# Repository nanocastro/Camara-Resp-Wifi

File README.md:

# Cámara de respiración de suelo

Prototipo portátil y de bajo costo para medir el flujo de CO2, la temperatura y la humedad del suelo y estimar su actividad microbiana.  

Este prototipo es parte del trabajo que estamos desarrollando en el [Laboratorio agroecológico abierto](https://regosh.libres.cc/proyectos/lab-agroeco-abierto/) y el nodo [ReGOSH de Mendoza](https://regosh.libres.cc/).

Su desarrollo está basado en el [prototipo abierto de Hackteria](https://www.hackteria.org/wiki/CO2_Soil_Respiration_Chamber).  

El costo de este prototipo es de 2 órdenes de magnitud menor que el de una [cámara comercial](https://gitlab.com/nanocastro/camara-respiracion-suelo/-/blob/master/Presupuestos%20Nro%2012426.PDF).  

## Prototipos
Estos prototipos están aún en fase de desarrollo. Necesitamos testear en campo y mejorar la documentación y el diseño.

### Prototipo actual - Versión Mendoza

Este prototipo utiliza el sensor de CO2 infrarrojo MH-Z19B que se coloca en el interior de una cámara para medir el flujo de CO2 y es controlado por una placa Arduino UNO. Los datos son transmitidos por bluetooth a un script de python que recibe los datos, los grafica en tiempo real y calcula la regresión lineal de un intervalo deseado. El dispositivo mide también la temperatura y la humedad de suelo

> [Aquí la documentación completa](/Version2-Mza) 

### Primer prototipo - Residencia Porto Alegre

[Primer prototipo](/Versión1-%20PA) desarrollado en el marco de la residencia ReGOSH (Porto Alegre) financiadas por CYTED.   
Este dispositivo utiliza un sensor MH-Z16 y una placa Teensy 4.0. Los datos se visualizan en una pantalla OLED

### Cómo funciona y para que sirve una cámara de respiración de suelo?
[Aqui](/Referencias) puedes encontrar algunos documentos que explican el funcionamiento de las cámaras de respiración de suelo y presentan algunos de sus usos

### Licencia 
Este proyecto es de código abierto y se libera bajo [licencia CERN para hardware abierto](https://gitlab.com/nanocastro/camara-respiracion-suelo/-/blob/master/License). 

### Te interesa colaborar?

Si te interesa el proyecto y quisieras colaborar podes escribirnos a 

ferhcastro at gmail.com o pcremades at gmail.com

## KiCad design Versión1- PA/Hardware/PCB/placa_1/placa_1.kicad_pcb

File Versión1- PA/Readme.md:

### Primer prototipo - Residencia Porto Alegre

[Primer prototipo](/Versión1-%20PA) desarrollado en el marco de la residencia ReGOSH (Porto Alegre) financiadas por CYTED.   
Este dispositivo utiliza un sensor MH-Z16 y una placa Teensy 4.0. Los datos se visualizan en una pantalla OLED

# Camara respiración de suelo - Residencia Porto Alegre

### Diseço de placa_ 

Acá se puede ver la placa en pcb de la cámara de respiración, como algunos complementos que fueron creados para el mismo 
https://gitlab.com/nodo-mendoza/camara-respiracion-suelo/tree/master/hardware/electronics
También pueden ver algunos inconvenientes que se nos presentaron aquí https://gitlab.com/nodo-mendoza/camara-respiracion-suelo/issues/3

### Fresadora_

Los archivos digitales para la fresadora se hicieron tomando como guía el siguiente trabajo
http://cta.if.ufrgs.br/projects/estacao-meteorologica-modular/wiki/Placa_de_Controle,
donde se modificaron parámetros de acuerdo a las características específicas del proyecto como del tipo de fresadora utilizada.
Lo anterior descripto se puede observar aqui https://gitlab.com/nodo-mendoza/camara-respiracion-suelo/tree/master/hardware/electronics/placa_1/gCode/ngc
imágenes dd157eda80d9fbdee688e2e542551893808dbe02

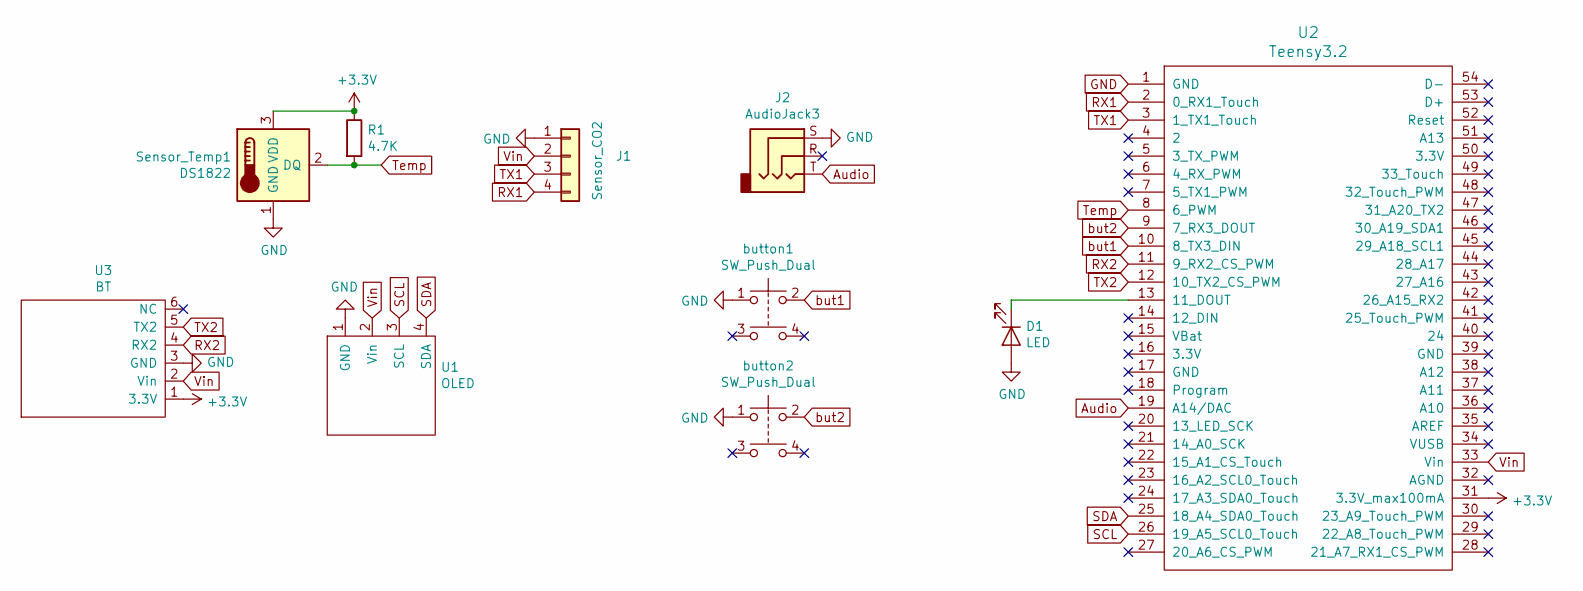
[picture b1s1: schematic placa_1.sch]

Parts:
D1: LED; LED_D3.0mm_IRBlack
J1: Sensor_CO2; PinHeader_1x04_P2.54mm_Vertical
J2: AudioJack3; AudioJack
R1: 4.7K; R_Axial_DIN0207_L6.3mm_D2.5mm_P7.62mm_Horizontal
Sensor_Temp1: DS1822; PinHeader_1x03_P2.54mm_Vertical
U1: OLED; PinHeader_1x04_P2.54mm_Vertical
U2: Teensy3.2; Teensy30_31_32_LC
U3: BT; PinHeader_1x06_P2.54mm_Vertical
button1, button2: SW_Push_Dual; SW_PUSH_6mm

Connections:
+3V3: R1.1, Sensor_Temp1.3 (VDD), U2.31 (3.3V_max100mA), U3.1 (3.3V)
Audio: J2.T, U2.19 (A14/DAC)
GND: D1.2 (A), J1.1, J2.S, Sensor_Temp1.1 (GND), U1.1 (GND), U2.1 (GND), U3.3 (GND), button1.1, button2.1
unnamed: D1.1 (K), U2.13 (11_DOUT)
RX1: J1.4, U2.2 (0_RX1_Touch)
RX2: U2.11 (9_RX2_CS_PWM), U3.4 (RX2)
SCL: U1.3 (SCL), U2.26 (19_A5_SCL0_Touch)
SDA: U1.4 (SDA), U2.25 (18_A4_SDA0_Touch)
TX1: J1.3, U2.3 (1_TX1_Touch)
TX2: U2.12 (10_TX2_CS_PWM), U3.5 (TX2)
Temp: R1.2, Sensor_Temp1.2 (DQ), U2.8 (6_PWM)
Vin: J1.2, U1.2 (Vin), U2.33 (Vin), U3.2 (Vin)
but1: U2.10 (8_TX3_DIN), button1.2
but2: U2.9 (7_RX3_DOUT), button2.2

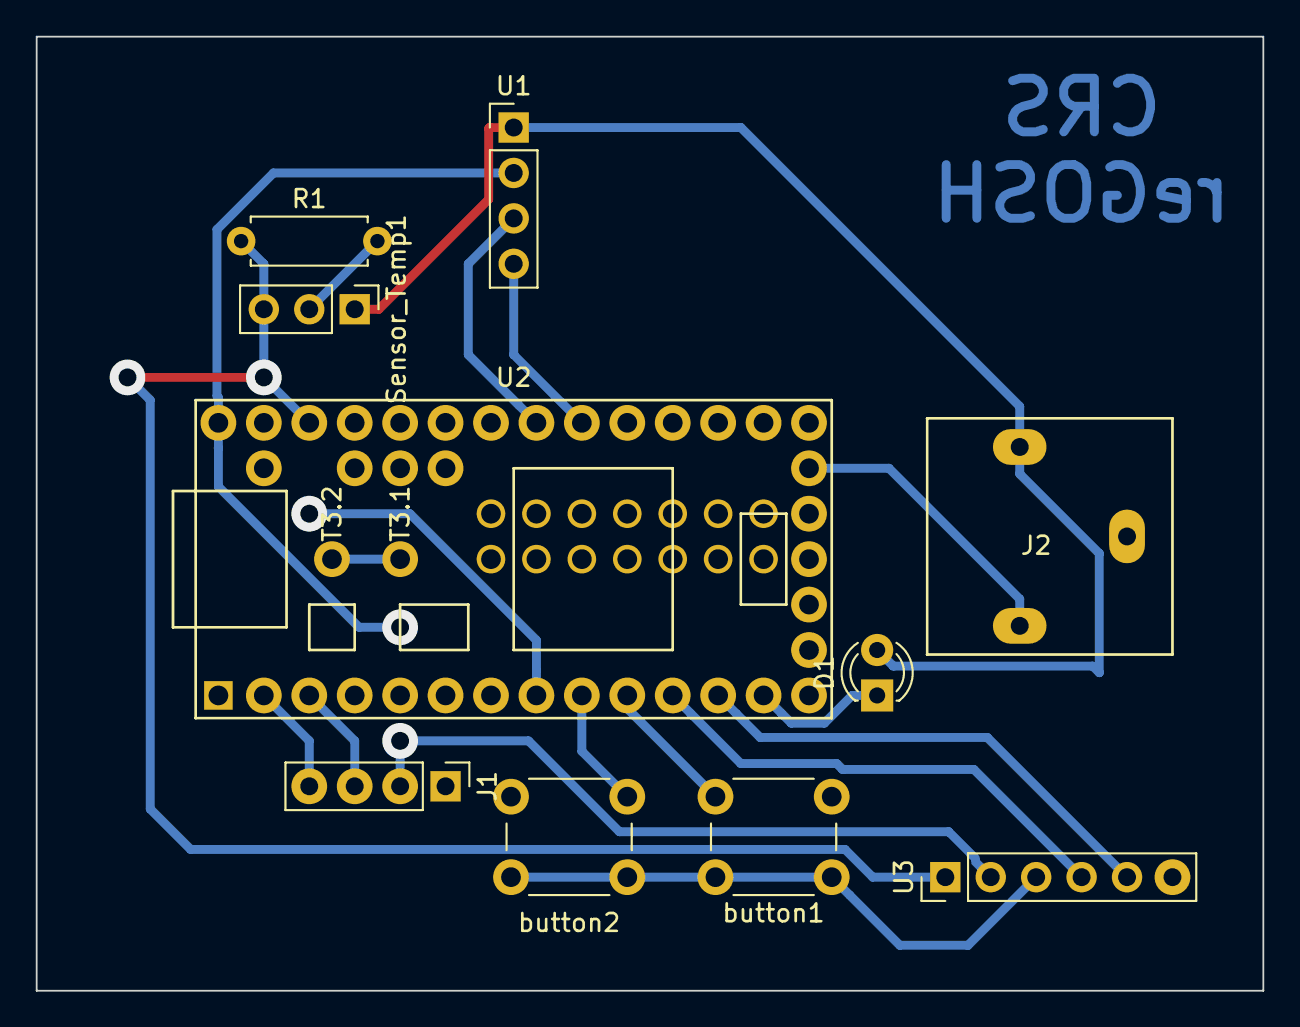
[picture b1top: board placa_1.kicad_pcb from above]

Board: 2 copper layers, 68.6 x 53.3 mm, 10 parts (0 on the bottom side), 14 nets.

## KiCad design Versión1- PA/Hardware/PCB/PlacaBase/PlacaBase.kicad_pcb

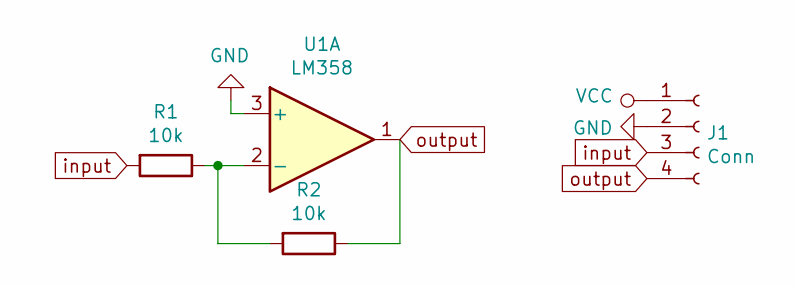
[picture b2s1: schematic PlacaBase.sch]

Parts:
J1: Conn; PinHeader_1x04_P1.00mm_Vertical
R1, R2: 10k; R_Axial_DIN0204_L3.6mm_D1.6mm_P5.08mm_Horizontal
U1: LM358; DIP-8_W7.62mm_Socket

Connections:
GND: J1.2, U1.3 (+)
unnamed: R1.1, R2.2, U1.2 (-)
VCC: J1.1
input: J1.3, R1.2
output: J1.4, R2.1, U1.1

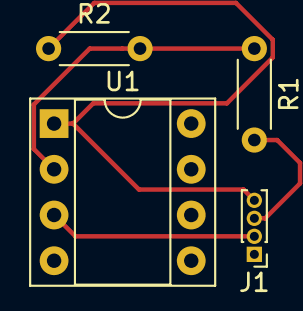
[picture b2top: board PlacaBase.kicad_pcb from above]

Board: 2 copper layers, 4 parts (0 on the bottom side), 4 nets.

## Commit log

2023-06-22 commit inicial
